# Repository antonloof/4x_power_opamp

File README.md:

# 4x_power_opamp
Four power amplifiers used for driving large ish loads from pwm ouputs

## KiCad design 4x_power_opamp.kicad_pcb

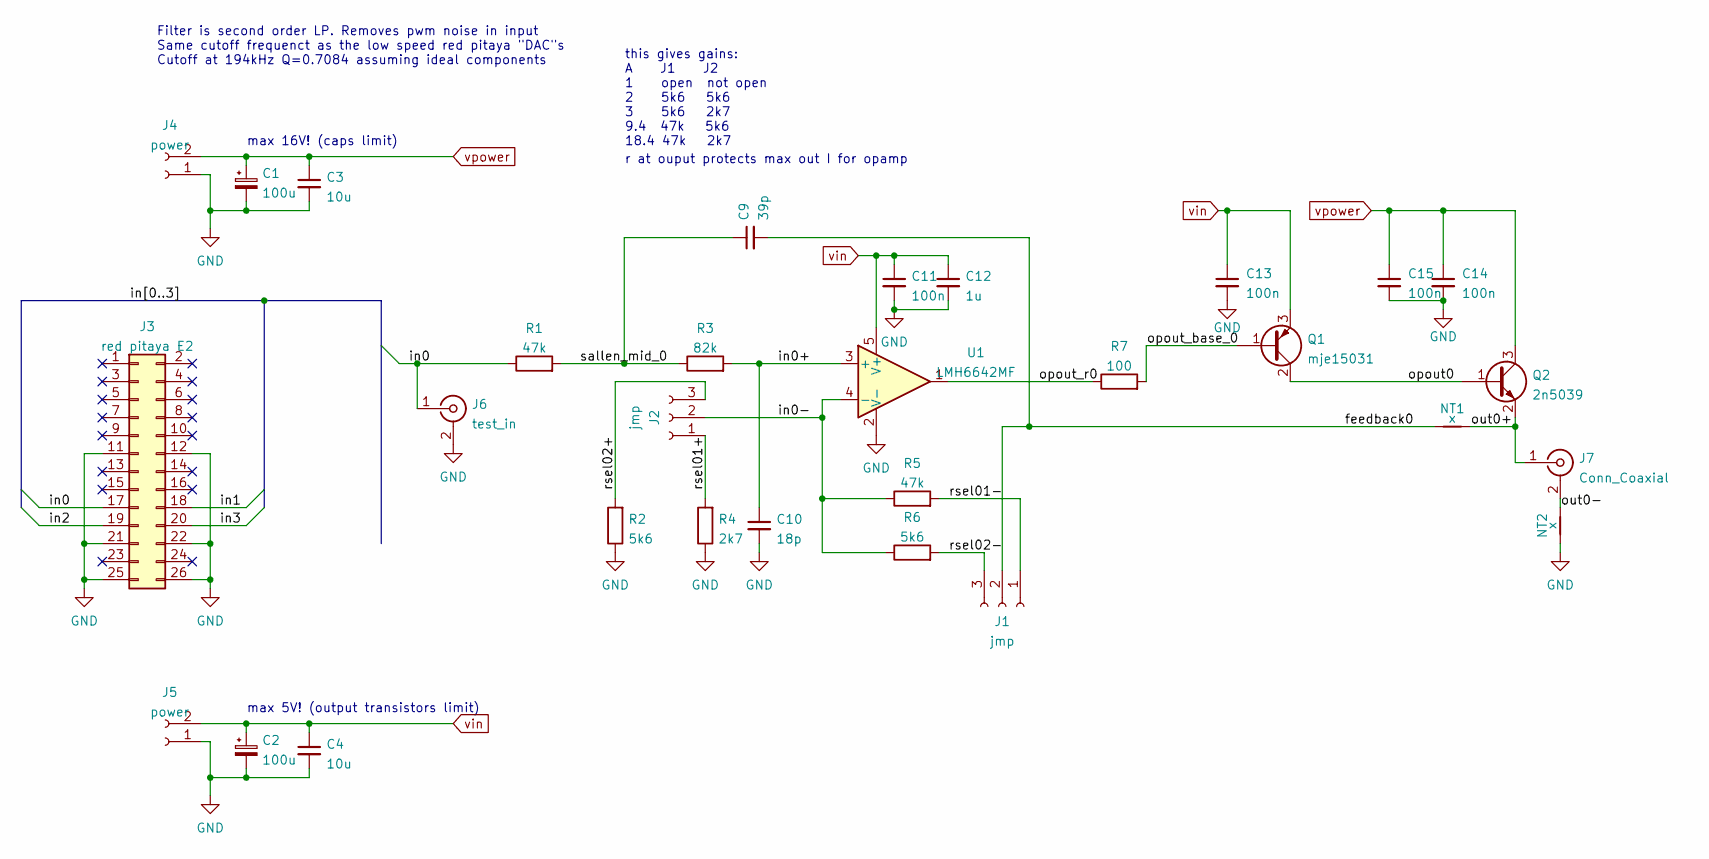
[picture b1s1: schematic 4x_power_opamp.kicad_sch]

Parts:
C1, C2: 100u; CP_Elec_10x10.5
C3, C4: 10u; C_0805_2012Metric_Pad1.18x1.45mm_HandSolder; part CL21A106KOQNNNE
C9: 39p; C_0603_1608Metric_Pad1.08x0.95mm_HandSolder; part C0603C104Z3VACTU
C10: 18p; C_0603_1608Metric_Pad1.08x0.95mm_HandSolder; part C0603C104Z3VACTU
C11, C13, C14, C15: 100n; C_0603_1608Metric_Pad1.08x0.95mm_HandSolder; part C0603C104Z3VACTU
C12: 1u; C_0603_1608Metric_Pad1.08x0.95mm_HandSolder; part CL10A105KA8NNNC
J1, J2: jmp; PinHeader_1x03_P2.54mm_Vertical
J3: red pitaya E2; IDC-Header_2x13_P2.54mm_Vertical
J4, J5: power; TerminalBlock_MetzConnect_Type094_RT03502HBLU_1x02_P5.00mm_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
J6: test_in; BNC_Amphenol_B6252HB-NPP3G-50_Horizontal
J7: Conn_Coaxial; BNC_Amphenol_B6252HB-NPP3G-50_Horizontal
NT1, NT2: x; NetTie-2_SMD_Pad0.5mm
Q1: mje15031; TO-220-3_Vertical
Q2: 2n5039; TO-3
R1, R5: 47k; R_0603_1608Metric_Pad0.98x0.95mm_HandSolder
R2, R6: 5k6; R_0603_1608Metric_Pad0.98x0.95mm_HandSolder
R3: 82k; R_0603_1608Metric_Pad0.98x0.95mm_HandSolder
R4: 2k7; R_0603_1608Metric_Pad0.98x0.95mm_HandSolder
R7: 100; R_0603_1608Metric_Pad0.98x0.95mm_HandSolder
U1: LMH6642MF; SOT-23-5

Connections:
/feedback0: C9.2, J1.2, NT1.1
/in0: J3.17, J6.1 (In), R1.1
/in0+: C10.1, R3.2, U1.3 (+)
/in0-: J2.2, R5.1, R6.1, U1.4 (-)
/opout0: Q1.2 (C), Q2.1 (B)
/opout_base_0: Q1.1 (B), R7.2
/opout_r0: R7.1, U1.1
/out0+: J7.1 (In), NT1.2, Q2.2 (E)
/out0-: J7.2 (Ext), NT2.2
/rsel01+: J2.1, R4.2
/rsel01-: J1.1, R5.2
/rsel02+: J2.3, R2.2
/rsel02-: J1.3, R6.2
/sallen_mid_0: C9.1, R1.2, R3.1
GND: C1.2, C2.2, C3.2, C4.2, C10.2, C11.2, C12.2, C13.2, C14.2, C15.2, J3.11, J3.12, J3.21, J3.22, J3.25, J3.26, J4.1, J5.1, J6.2 (Ext), NT2.1, R2.1, R4.1, U1.2 (V-)
vin: C2.1, C4.1, C11.1, C12.1, C13.1, J5.2, Q1.3 (E), U1.5 (V+)
vpower: C1.1, C3.1, C14.1, C15.1, J4.2, Q2.3 (C)

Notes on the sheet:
Filter is second order LP. Removes pwm noise in input Same cutoff frequenct as the low speed red pitaya "DAC"s Cutoff at 194kHz Q=0.7084 assuming ideal components
this gives gains: A J1 J2 1 open not open 2 5k6 5k6 3 5k6 2k7 9.4 47k 5k6 18.4 47k 2k7
max 16V! (caps limit)
max 5V! (output transistors limit)
r at ouput protects max out I for opamp

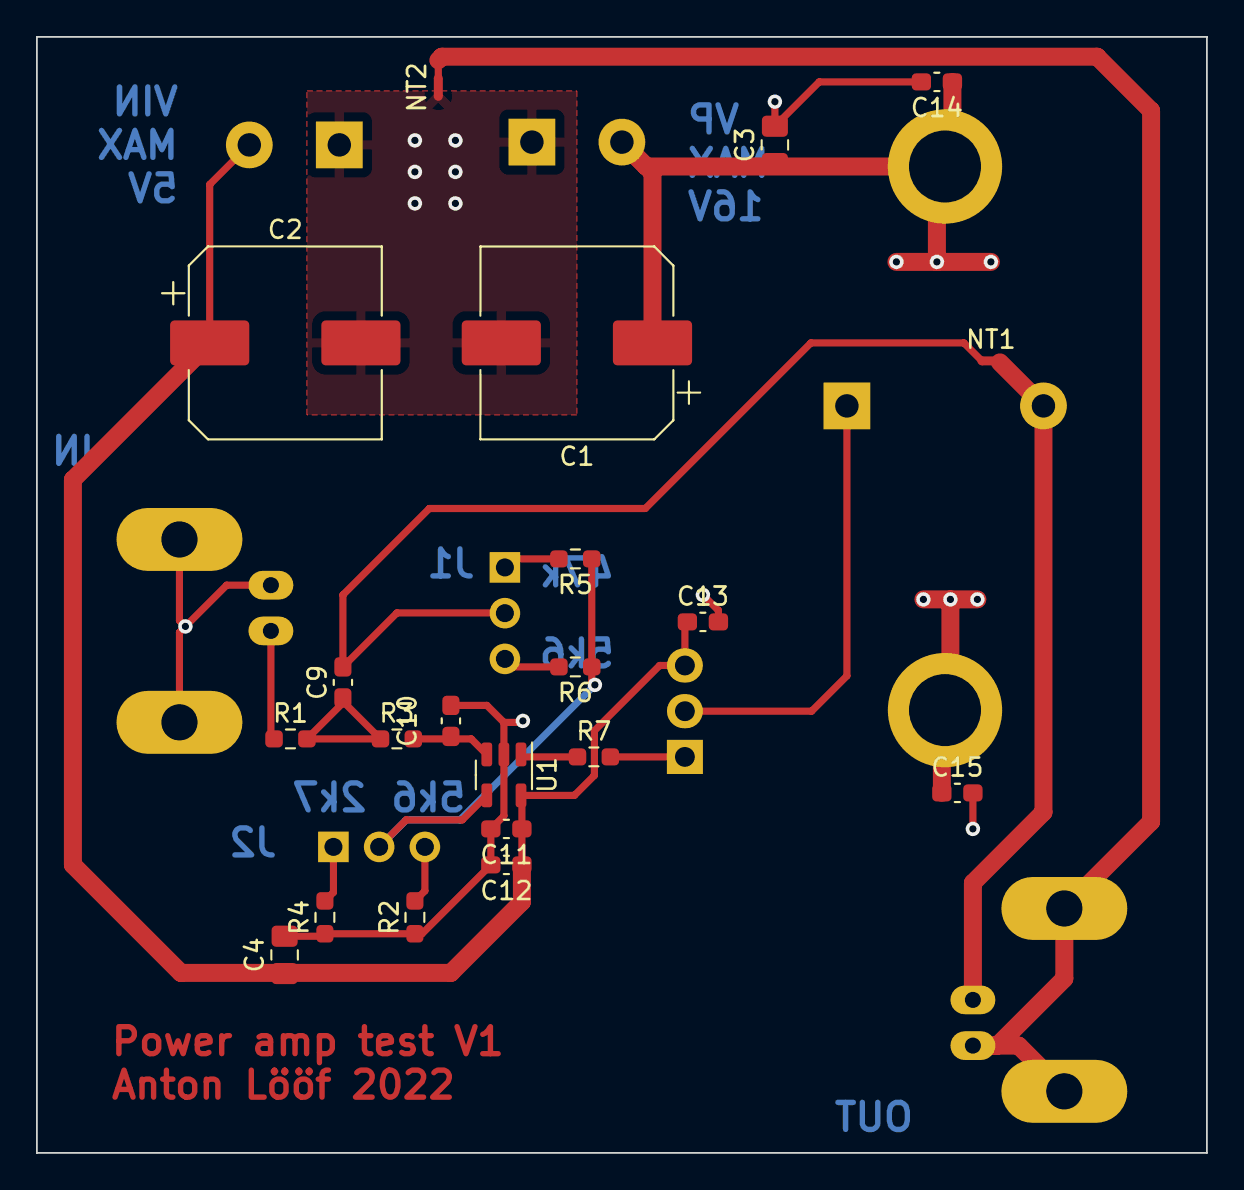
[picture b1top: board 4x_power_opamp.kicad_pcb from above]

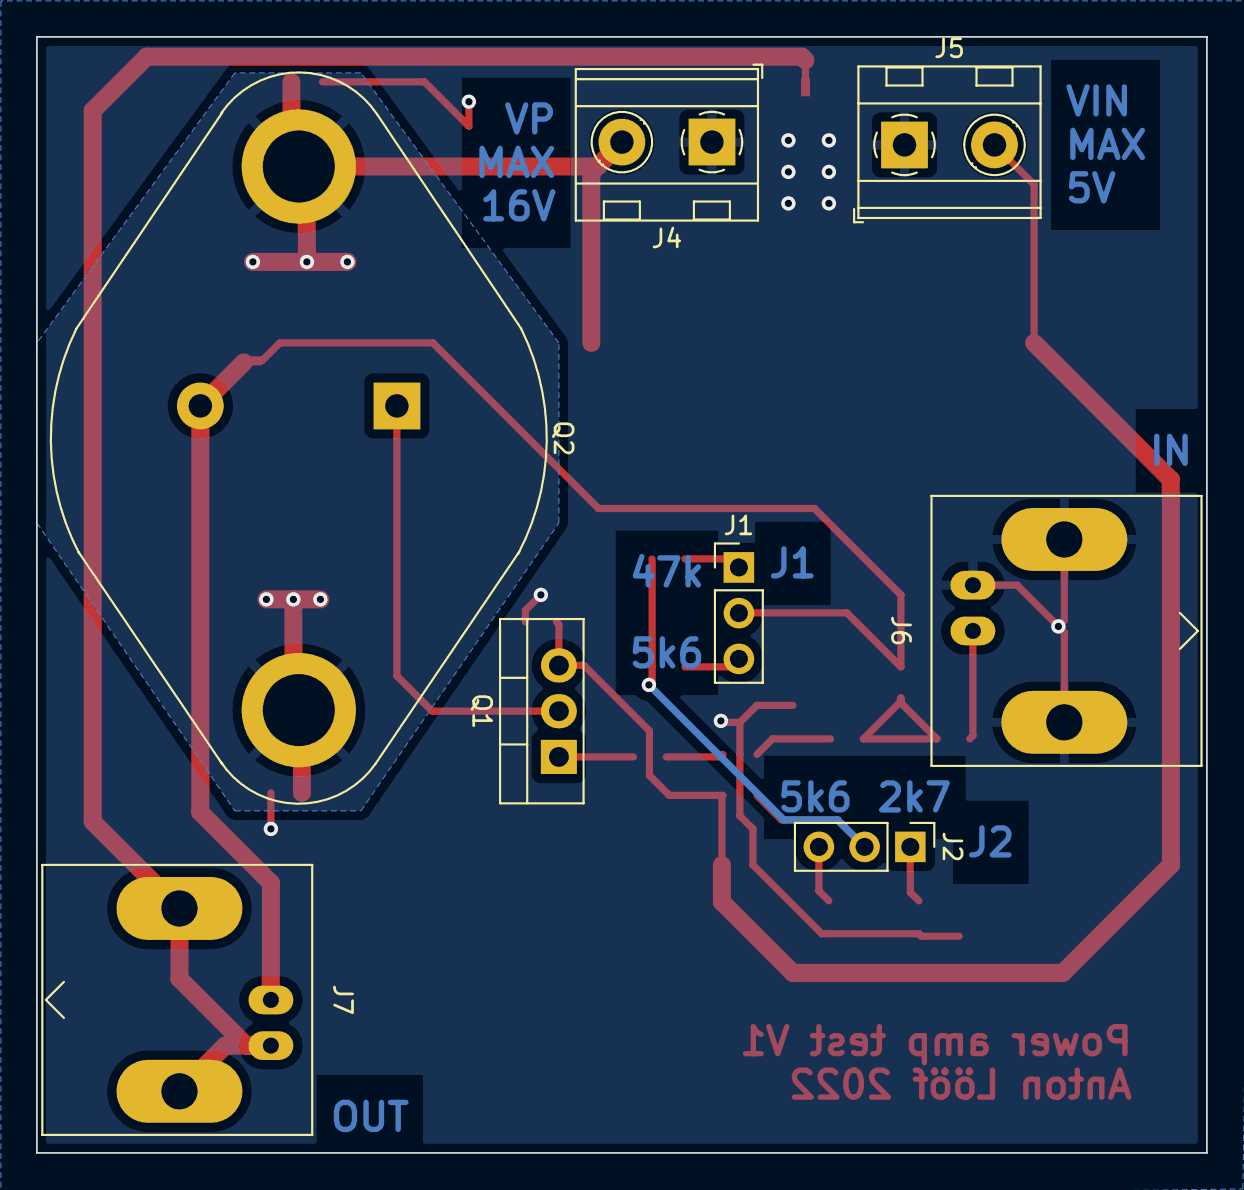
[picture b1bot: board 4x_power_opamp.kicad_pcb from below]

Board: 2 copper layers, 65.0 x 62.0 mm, 29 parts (8 on the bottom side), 17 nets.

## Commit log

2022-01-21 Add some schema and fun matlab tools for calculating passives
2022-01-22 Test pcb done, and made
2022-01-22 rm pdfs
2022-01-22 Add simulation of filter
    also take gain of filter into account for Q calculation
